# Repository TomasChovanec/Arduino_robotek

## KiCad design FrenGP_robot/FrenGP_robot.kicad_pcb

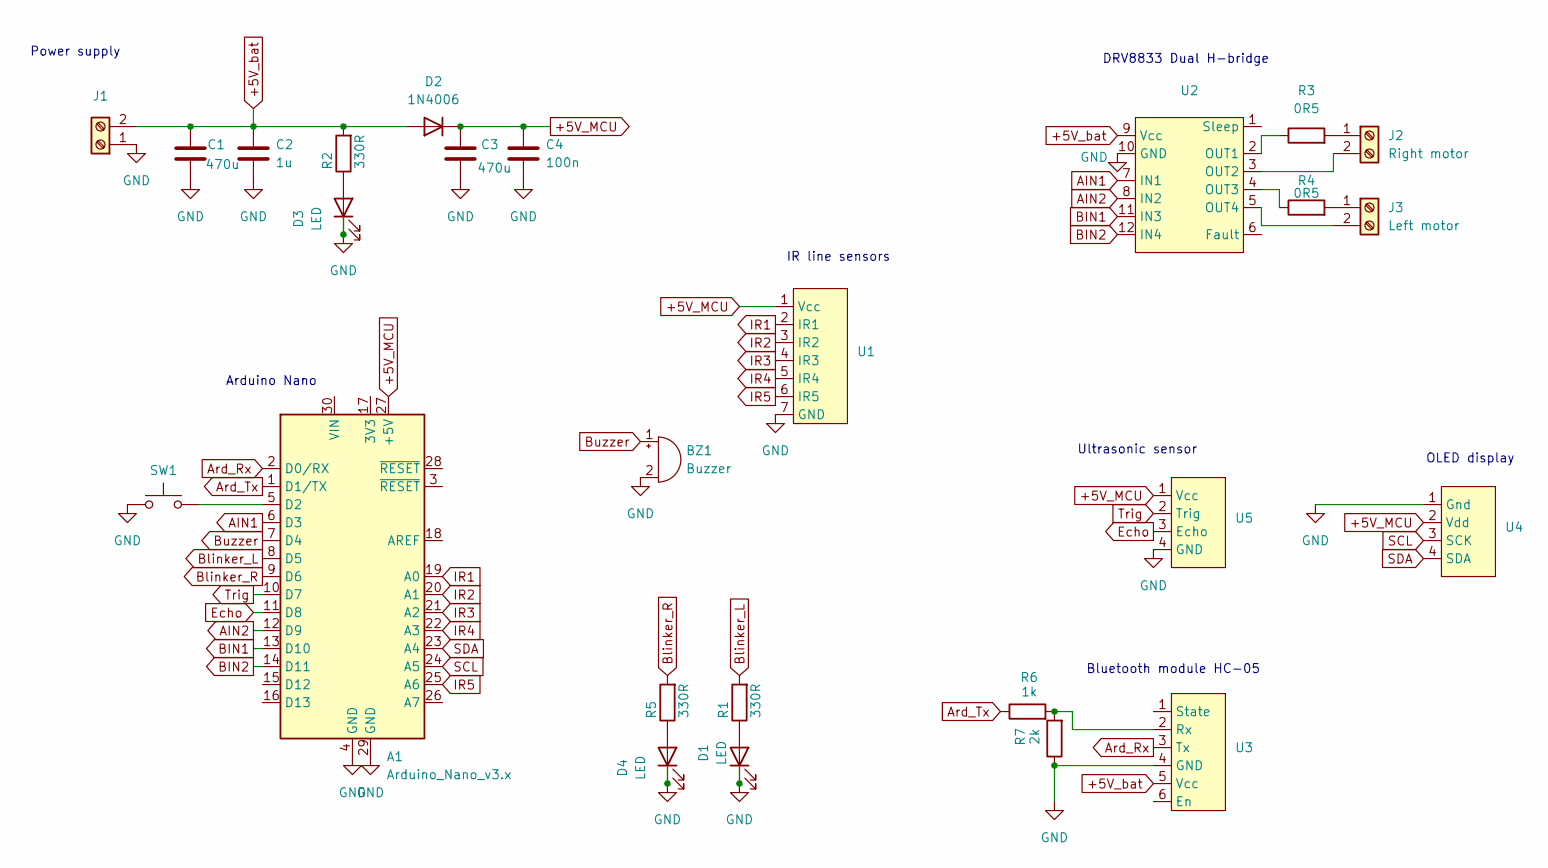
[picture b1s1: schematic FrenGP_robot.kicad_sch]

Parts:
A1: Arduino_Nano_v3.x; Arduino_Nano
BZ1: Buzzer; Buzzer_12x9.5RM7.6
C1, C3: 470u; CP_Elec_8x6.2
C2: 1u; C_0603_1608Metric_Pad1.08x0.95mm_HandSolder
C4: 100n; C_0603_1608Metric_Pad1.08x0.95mm_HandSolder
D1, D3, D4: LED; D_0603_1608Metric_Pad1.05x0.95mm_HandSolder
D2: 1N4006; D_SMA-SMB_Universal_Handsoldering
J1: Screw_Terminal_01x02; TerminalBlock_bornier-2_P5.08mm
J2: Right motor; TerminalBlock_bornier-2_P5.08mm
J3: Left motor; TerminalBlock_bornier-2_P5.08mm
R1, R2, R5: 330R; R_0603_1608Metric_Pad0.98x0.95mm_HandSolder
R3, R4: 0R5; R_0805_2012Metric_Pad1.20x1.40mm_HandSolder
R6: 1k; R_0603_1608Metric_Pad0.98x0.95mm_HandSolder
R7: 2k; R_0603_1608Metric_Pad0.98x0.95mm_HandSolder
SW1: SW_Push; SW_PUSH_6mm
U1: IR sensor header
U2: DIP-12_W15.24mm
U3: HC-05 header
U4: OLED display header
U5: HC-SR04_module

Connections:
+5V_MCU: A1.27 (+5V), C3.1, C4.1, D2.1 (K), U1.1 (Vcc), U4.2 (Vdd), U5.1 (Vcc)
+5V_bat: C1.1, C2.1, D2.2 (A), J1.2, R2.2, U2.9 (Vcc), U3.5 (Vcc)
AIN1: A1.6 (D3), U2.7 (IN1)
AIN2: A1.12 (D9), U2.8 (IN2)
Ard_Rx: A1.2 (D0/RX), U3.3 (Tx)
Ard_Tx: A1.1 (D1/TX), R6.1
BIN1: A1.13 (D10), U2.11 (IN3)
BIN2: A1.14 (D11), U2.12 (IN4)
Blinker_L: A1.8 (D5), R1.2
Blinker_R: A1.9 (D6), R5.2
Buzzer: A1.7 (D4), BZ1.1 (+)
Echo: A1.11 (D8), U5.3 (Echo)
GND: A1.4 (GND), A1.29 (GND), BZ1.2 (-), C1.2, C2.2, C3.2, C4.2, D1.1 (K), D3.1 (K), D4.1 (K), J1.1, R7.1, SW1.1, U1.7 (GND), U2.10 (GND), U3.4 (GND), U4.1 (Gnd), U5.4 (GND)
IR1: A1.19 (A0), U1.2 (IR1)
IR2: A1.20 (A1), U1.3 (IR2)
IR3: A1.21 (A2), U1.4 (IR3)
IR4: A1.22 (A3), U1.5 (IR4)
IR5: A1.25 (A6), U1.6 (IR5)
unnamed: A1.5 (D2), SW1.2
unnamed: D1.2 (A), R1.1
unnamed: D3.2 (A), R2.1
unnamed: D4.2 (A), R5.1
unnamed: J2.1, R3.2
unnamed: J2.2, U2.3 (OUT2)
unnamed: J3.1, R4.2
unnamed: J3.2, U2.5 (OUT4)
unnamed: R3.1, U2.2 (OUT1)
unnamed: R4.1, U2.4 (OUT3)
unnamed: R6.2, R7.2, U3.2 (Rx)
SCL: A1.24 (A5), U4.3 (SCK)
SDA: A1.23 (A4), U4.4 (SDA)
Trig: A1.10 (D7), U5.2 (Trig)

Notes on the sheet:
Power supply
Bluetooth module HC-05
Ultrasonic sensor
Arduino Nano
IR line sensors
OLED display
DRV8833 Dual H-bridge

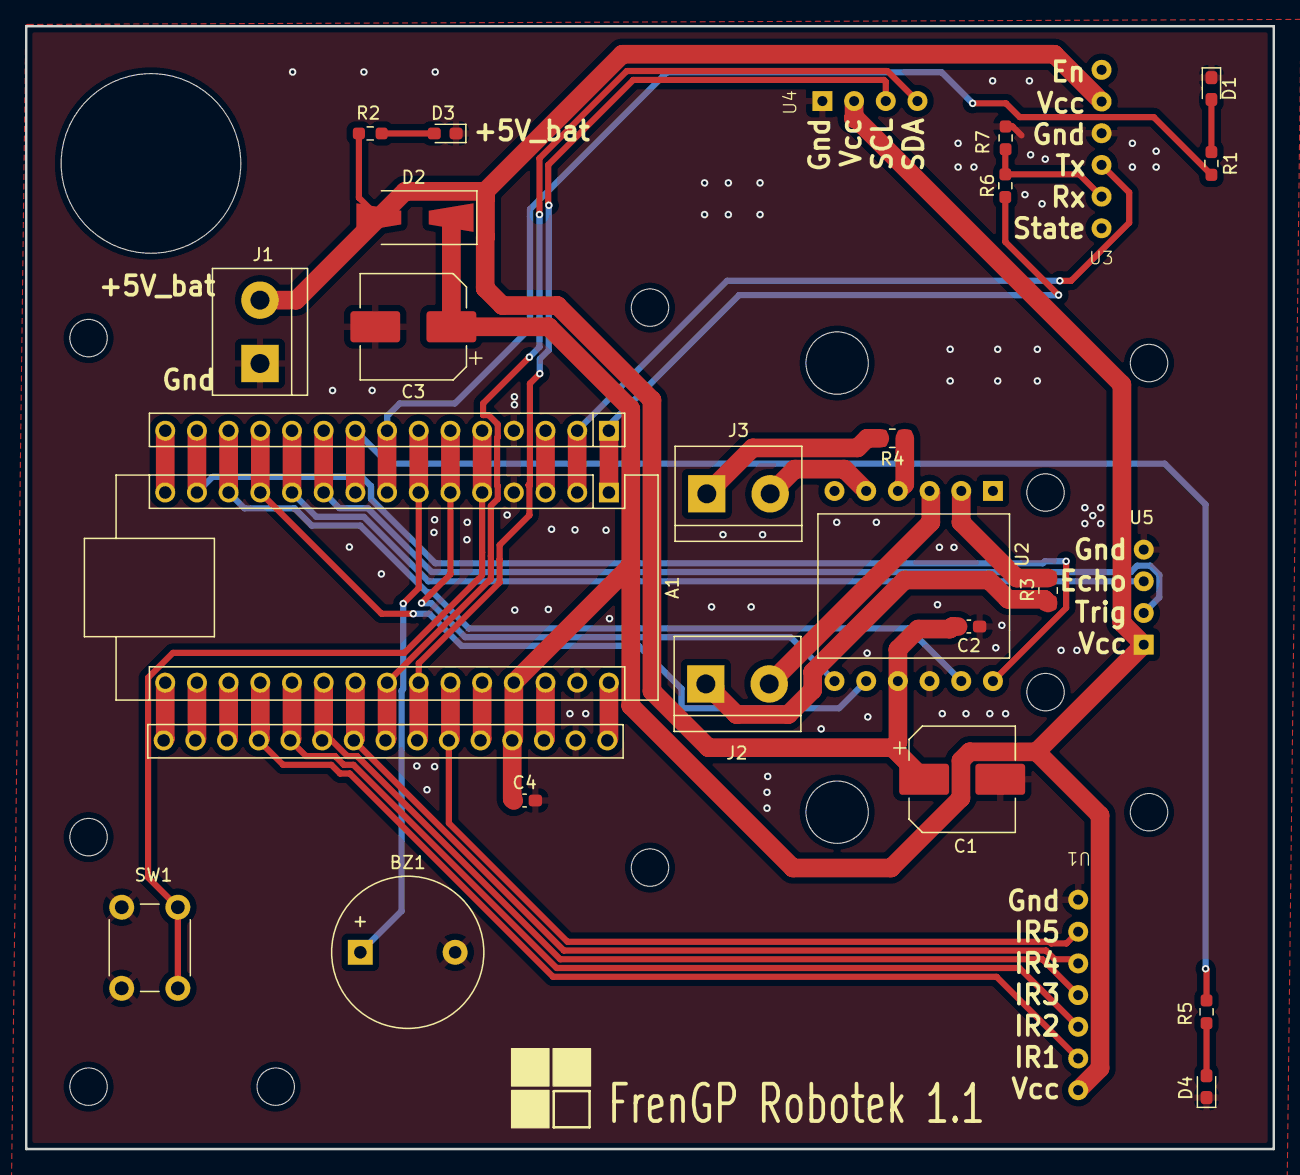
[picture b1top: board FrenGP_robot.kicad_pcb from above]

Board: 2 copper layers, 100.0 x 90.0 mm, 26 parts (0 on the bottom side), 32 nets.

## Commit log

2024-09-22 Update gerber
2024-09-28 Hide models for IR sensors
2024-09-28 Gerbers added
2024-09-28 Release folder created
2024-10-16 Manual added COmponent list update
2024-10-16 Schematics update
2025-06-03 Update to KiCAD 9 Fixed Ultrasonic sensor footprint
2025-06-03 Buzzer HC-05 LED blinkers Second pin rows
2025-06-04 Footprints added
2025-06-10 Rev 1.1 finished
2025-06-11 Schematics added
2025-10-01 Assembly manual added
